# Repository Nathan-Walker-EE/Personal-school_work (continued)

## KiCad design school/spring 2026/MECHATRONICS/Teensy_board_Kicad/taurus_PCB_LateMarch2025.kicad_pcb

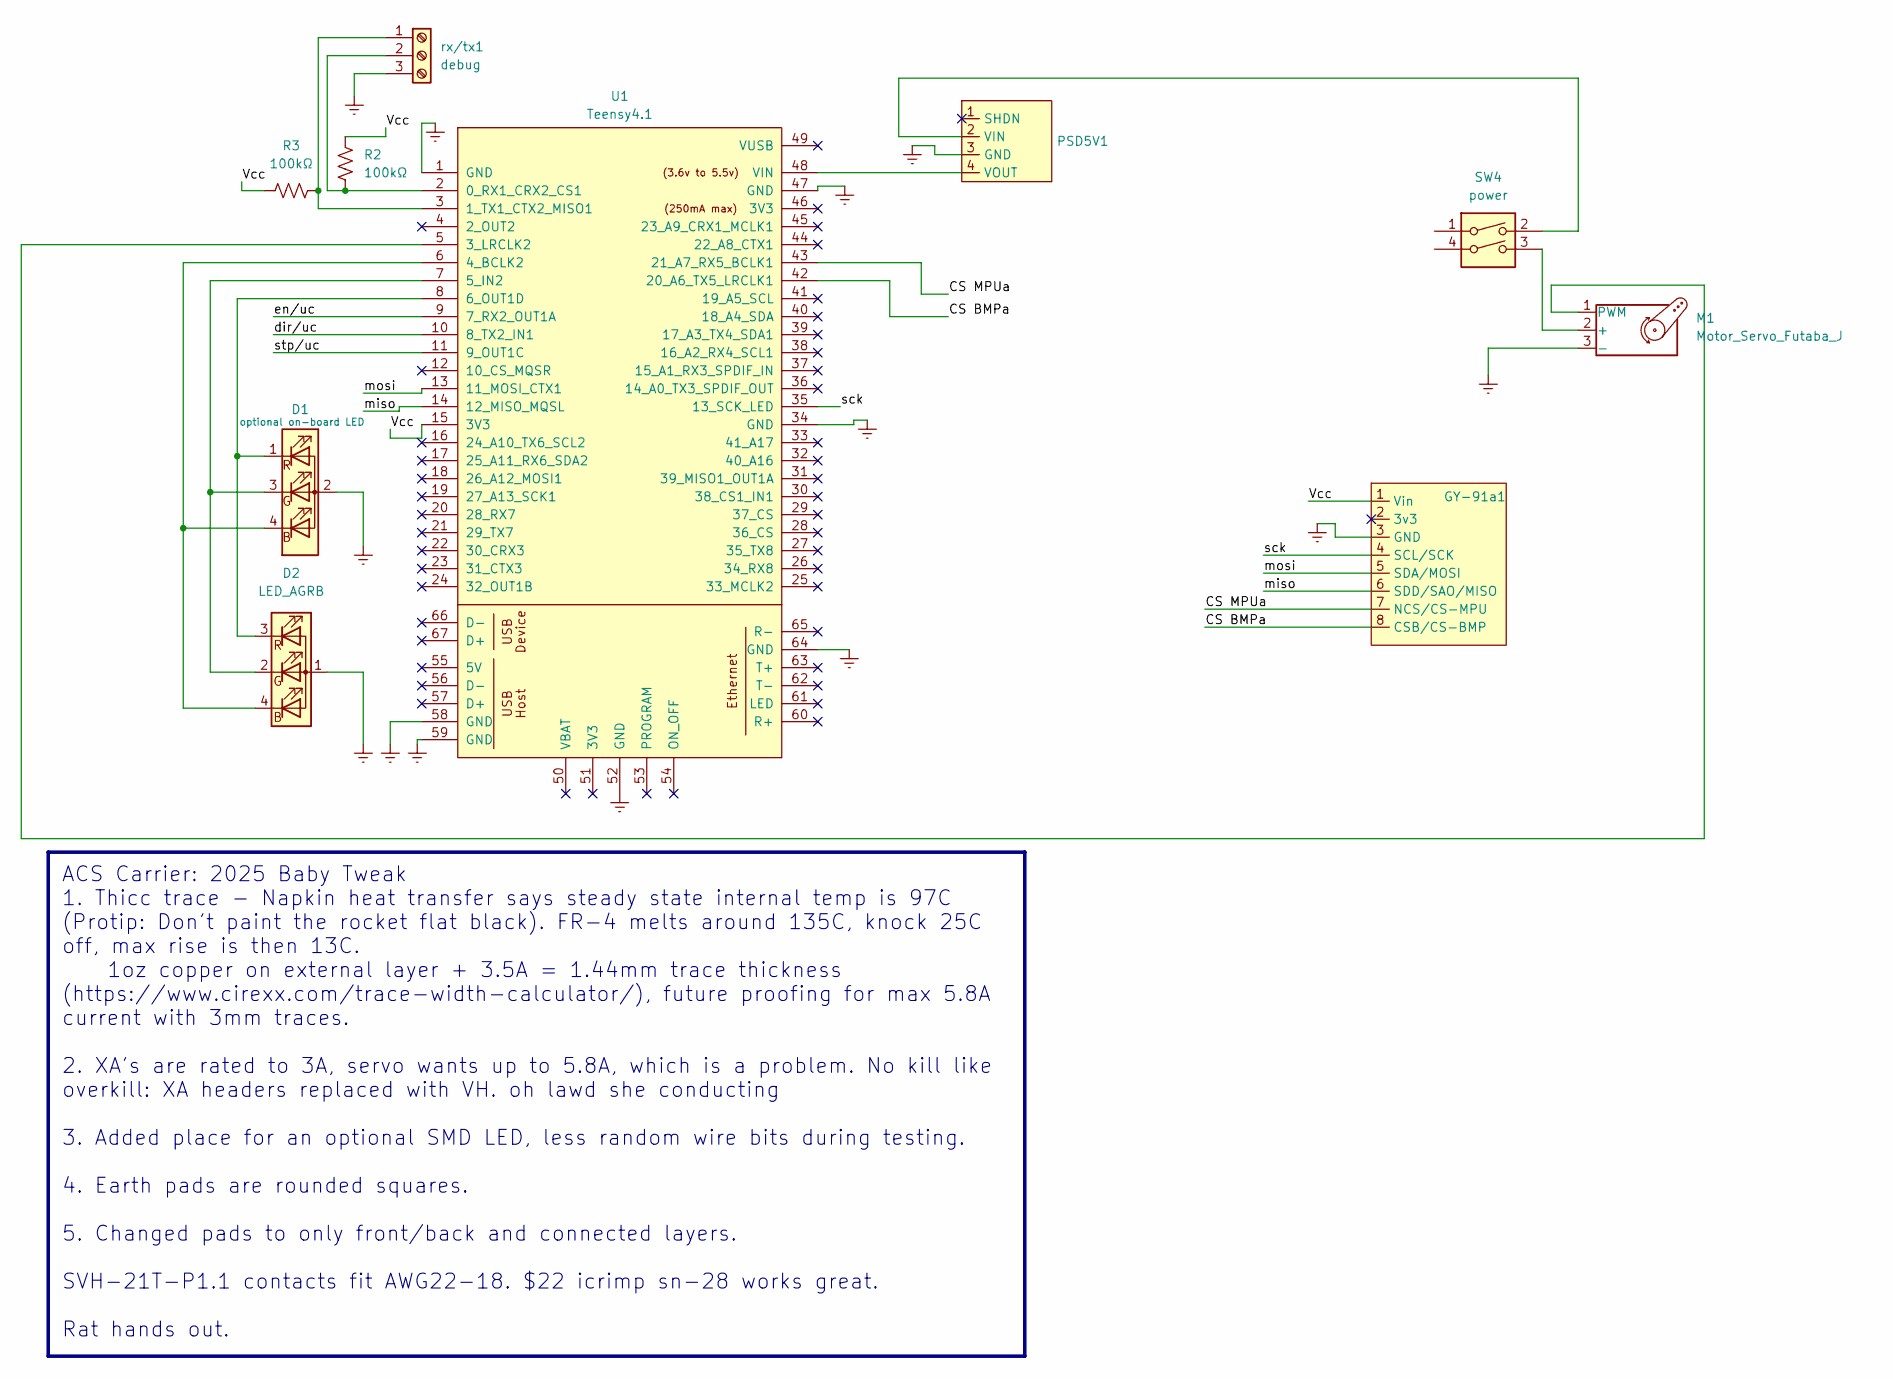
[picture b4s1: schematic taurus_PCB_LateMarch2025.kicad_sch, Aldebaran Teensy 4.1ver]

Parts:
D1: optional on-board LED; LED_Avago_PLCC4_3.2x2.8mm_CW
D2: LED_AGRB; JST_XA_B04B-XASK-1-A_1x04_P2.50mm_Vertical
GY-91a1: GY-91 carrier
M1: Motor_Servo_Futaba_J; JST_VH_B3P-VH-FB-B_1x03_P3.96mm_Vertical
PSD5V1: Pololu 5V0.6A stepdown
R2, R3: 100kΩ; C_0805_2012Metric_Pad1.18x1.45mm_HandSolder
SW4: power; JST_VH_B4P-VH-FB-B_1x04_P3.96mm_Vertical
U1: Teensy4.1; Teensy41
rx/tx1: debug; JST_VH_B3P-VH-FB-B_1x03_P3.96mm_Vertical

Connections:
/CS BMPa: GY-91a1.8 (CSB/CS-BMP), U1.42 (20_A6_TX5_LRCLK1)
/CS MPUa: GY-91a1.7 (NCS/CS-MPU), U1.43 (21_A7_RX5_BCLK1)
/Vcc: GY-91a1.1 (Vin), R2.2, R3.1, U1.15 (3V3)
/dir/uc: U1.10 (8_TX2_IN1)
/en/uc: U1.9 (7_RX2_OUT1A)
/miso: GY-91a1.6 (SDD/SAO/MISO), U1.14 (12_MISO_MQSL)
/mosi: GY-91a1.5 (SDA/MOSI), U1.13 (11_MOSI_CTX1)
/sck: GY-91a1.4 (SCL/SCK), U1.35 (13_SCK_LED)
/stp/uc: U1.11 (9_OUT1C)
Earth: D1.2 (A), D2.1 (A), GY-91a1.3 (GND), M1.3 (-), PSD5V1.3 (GND), SW4.1, SW4.4, U1.1 (GND), U1.34 (GND), U1.47 (GND), U1.52 (GND), U1.58 (GND), U1.59 (GND), U1.64 (GND), rx/tx1.3
unnamed: D1.4 (BK), D2.4 (BK), U1.6 (4_BCLK2)
unnamed: D1.3 (GK), D2.2 (GK), U1.7 (5_IN2)
unnamed: D1.1 (RK), D2.3 (RK), U1.8 (6_OUT1D)
unnamed: M1.2 (+), SW4.3
unnamed: M1.1 (PWM), U1.5 (3_LRCLK2)
unnamed: PSD5V1.2 (VIN), SW4.2
unnamed: PSD5V1.4 (VOUT), U1.48 (VIN)
unnamed: R2.1, U1.2 (0_RX1_CRX2_CS1), rx/tx1.2
unnamed: R3.2, U1.3 (1_TX1_CTX2_MISO1), rx/tx1.1

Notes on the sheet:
ACS Carrier: 2025 Baby Tweak 1. Thicc trace - Napkin heat transfer says steady state internal temp is 97C (Protip: Don't paint the rocket flat black). FR-4 melts around 135C, knock 25C off, max rise is then 13C. 1oz copper on external layer + 3.5A = 1.44mm trace thickness (https://www.cirexx.com/tr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

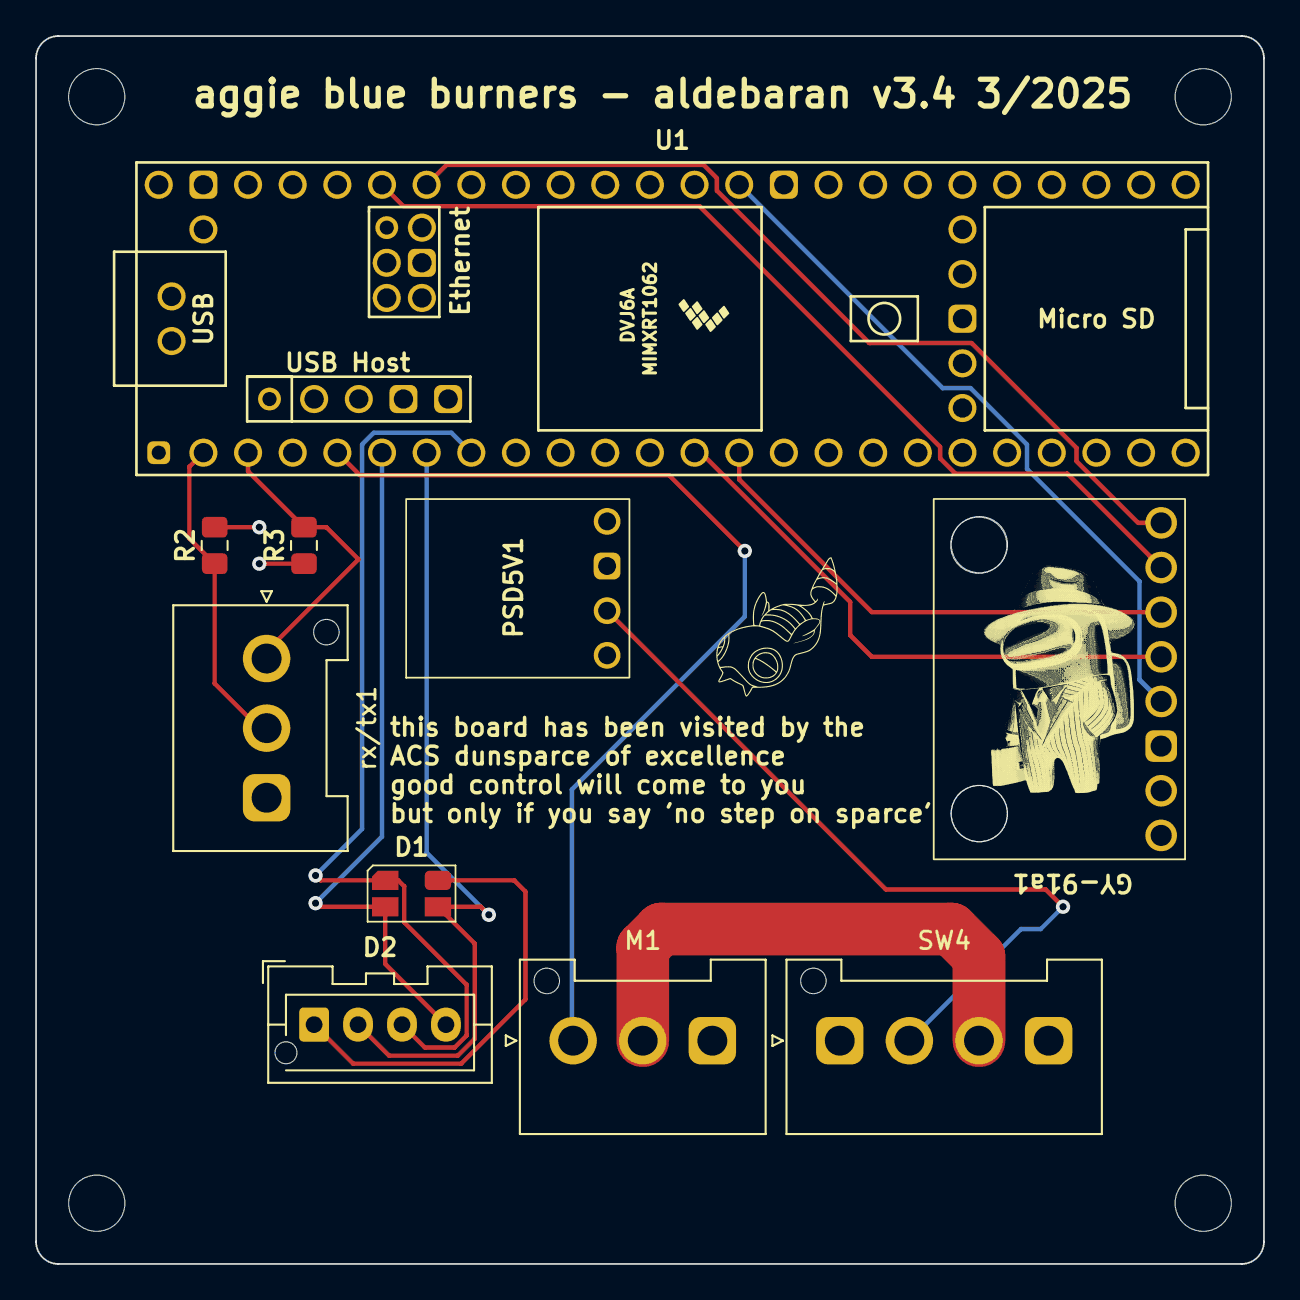
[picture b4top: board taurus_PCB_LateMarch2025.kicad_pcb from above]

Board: 4 copper layers, 69.9 x 69.9 mm, 14 parts (0 on the bottom side), 16 nets.

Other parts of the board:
refhole1, refhole2, refhole3, refhole4: MountingHole_3.2mm_M3

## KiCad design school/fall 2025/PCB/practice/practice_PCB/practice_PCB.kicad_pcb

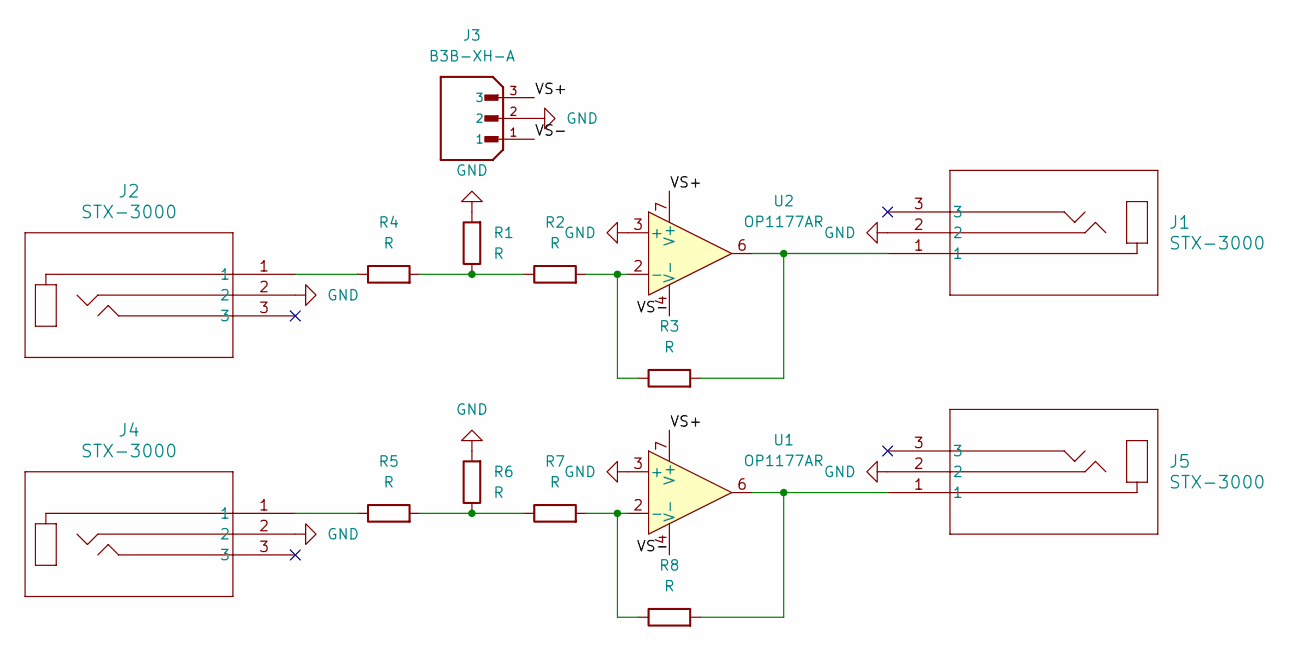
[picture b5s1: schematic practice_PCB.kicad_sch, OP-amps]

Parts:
J1, J2, J4, J5: STX-3000; STX-3000_KYC
J3: B3B-XH-A; JST_B3B-XH-A; PARTREV 7/4/21
R1, R2, R3, R4, R5, R6, R7, R8: R; R_0201_0603Metric
U1, U2: OP1177AR; SOIC-8_3.9x4.9mm_P1.27mm

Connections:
/VS+: J3.3, U1.7 (V+), U2.7 (V+)
/VS-: J3.1, U1.4 (V-), U2.4 (V-)
GND: J1.2, J2.2, J3.2, J4.2, J5.2, R1.2, R6.2, U1.3 (+), U2.3 (+)
unnamed: J1.1, R3.2, U2.6
unnamed: J2.1, R4.1
unnamed: J4.1, R5.1
unnamed: J5.1, R8.2, U1.6
unnamed: R1.1, R2.1, R4.2
unnamed: R5.2, R6.1, R7.1
unnamed: R7.2, R8.1, U1.2 (-)
unnamed: R2.2, R3.1, U2.2 (-)

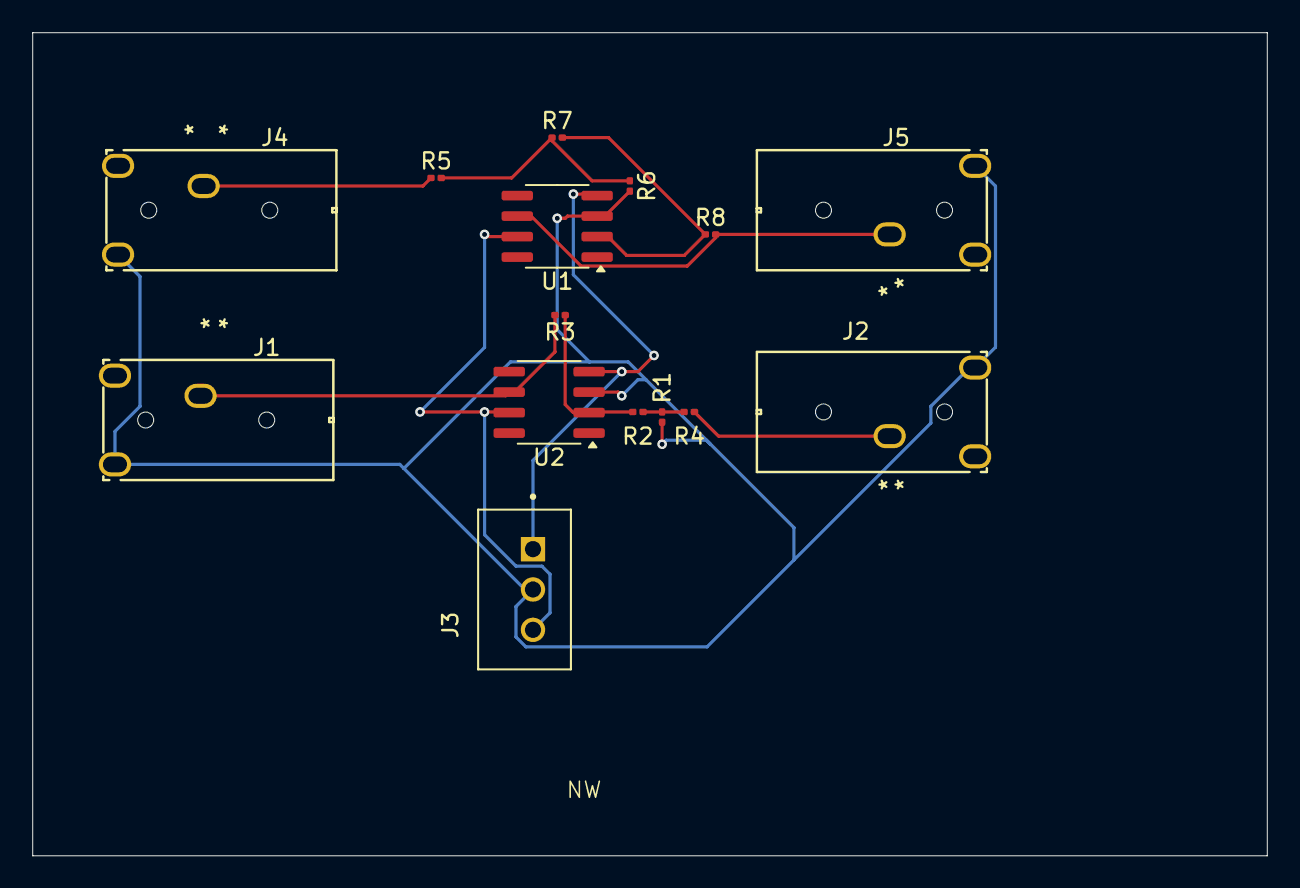
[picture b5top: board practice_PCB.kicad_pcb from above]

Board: 2 copper layers, 76.5 x 51.0 mm, 15 parts (0 on the bottom side), 11 nets.

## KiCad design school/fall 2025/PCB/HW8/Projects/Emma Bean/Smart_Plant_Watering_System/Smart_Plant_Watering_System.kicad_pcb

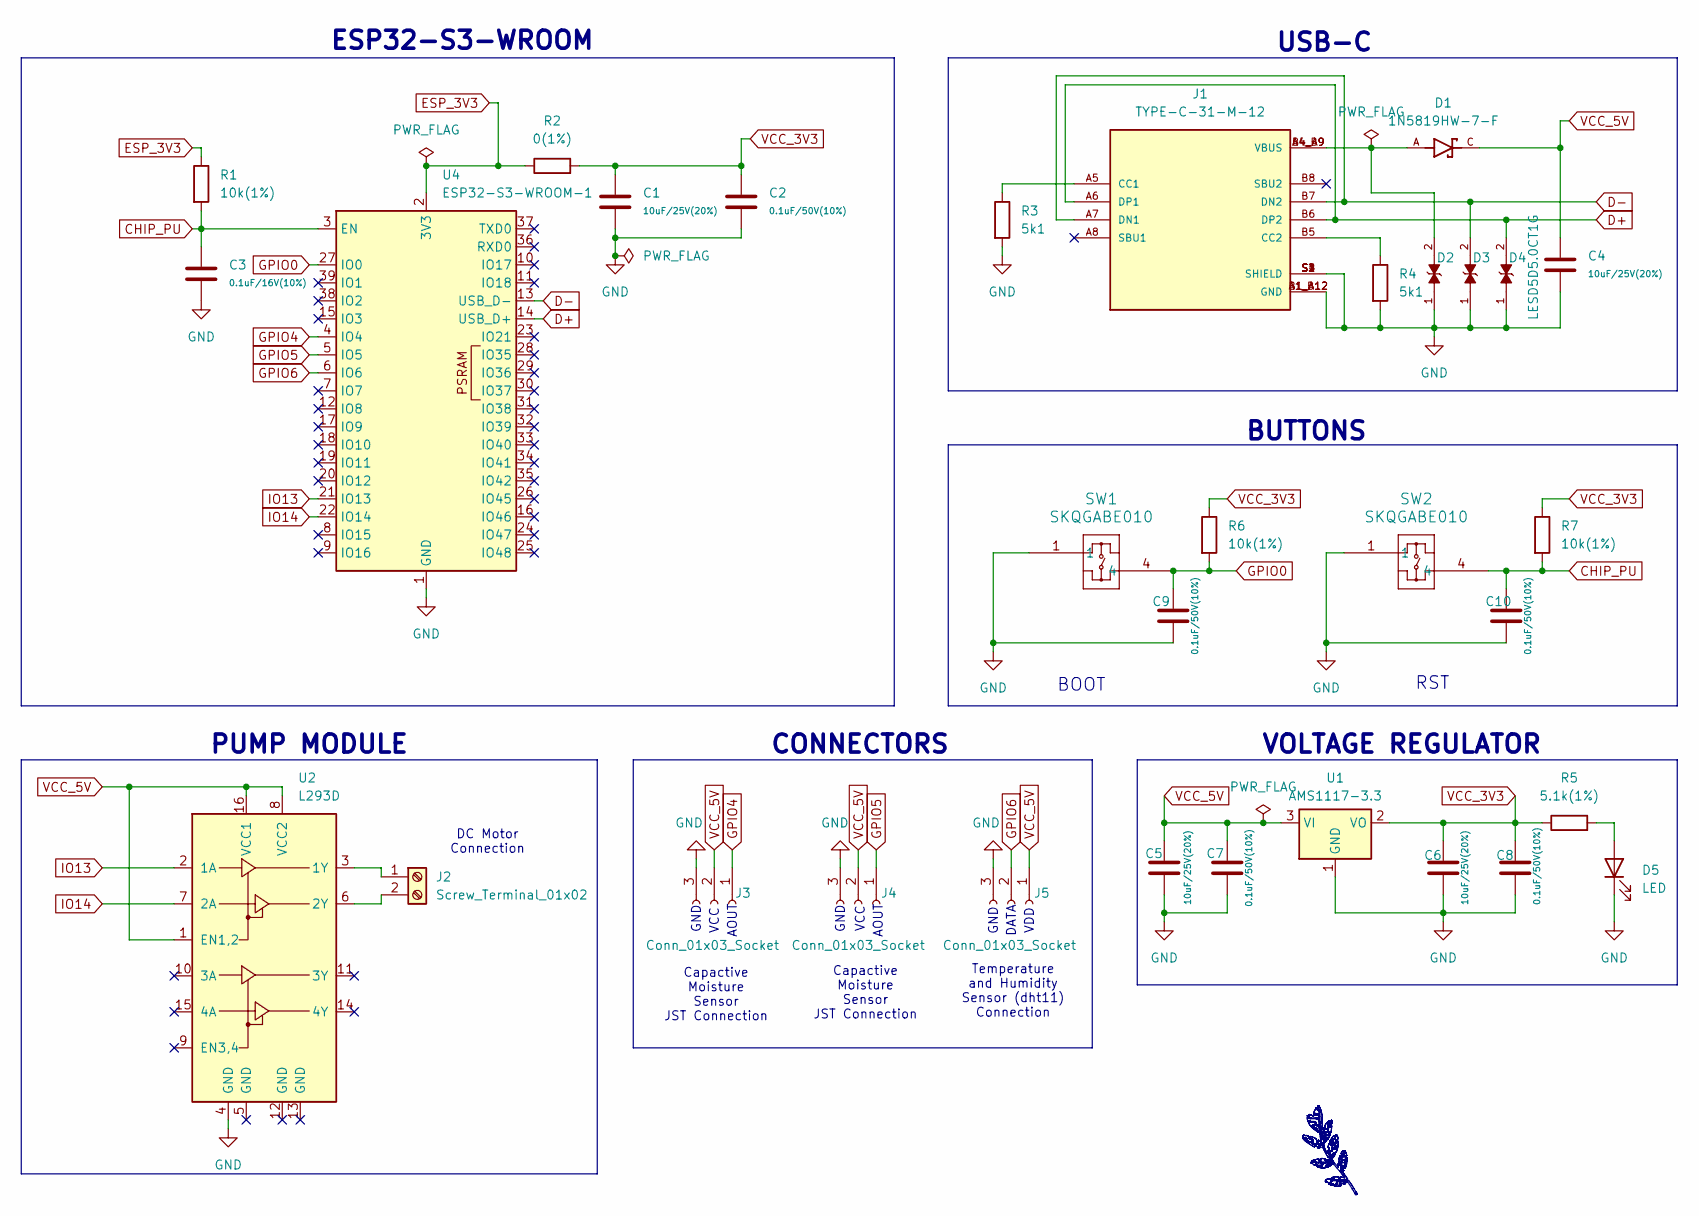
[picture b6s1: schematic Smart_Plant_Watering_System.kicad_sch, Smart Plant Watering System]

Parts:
C1, C4, C5, C6: 10uF/25V(20%); C_0805_2012Metric_Pad1.18x1.45mm_HandSolder
C2, C7, C8, C9, C10: 0.1uF/50V(10%); C_0805_2012Metric_Pad1.18x1.45mm_HandSolder
C3: 0.1uF/16V(10%); C_0805_2012Metric_Pad1.18x1.45mm_HandSolder
D1: 1N5819HW-7-F; SOD3715X145N; PARTREV 18-2; DigiKey_Part_Number 1N5819HW-FDICT-ND
D2, D3, D4: LESD5D5.0CT1G; D_SOD-523; PARTREV O
D5: LED; LED_0201_0603Metric
J1: TYPE-C-31-M-12; HRO_TYPE-C-31-M-12; PARTREV 2020.12.08
J2: Screw_Terminal_01x02; 691137710002
J3, J4, J5: Conn_01x03_Socket; JST_XH_B3B-XH-A_1x03_P2.50mm_Vertical
R1, R6, R7: 10k(1%); R_0805_2012Metric_Pad1.20x1.40mm_HandSolder
R2: 0(1%); R_0805_2012Metric_Pad1.20x1.40mm_HandSolder
R3, R4: 5k1; R_0805_2012Metric_Pad1.20x1.40mm_HandSolder
R5: 5.1k(1%); R_0805_2012Metric_Pad1.20x1.40mm_HandSolder
SW1, SW2: SKQGABE010; SKQGABE010_ALPS
U1: AMS1117-3.3; SOT-223-3_TabPin2
U2: L293D; DIP-16_W7.62mm
U4: ESP32-S3-WROOM-1

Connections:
CHIP_PU: C3.1, C10.1, R1.2, R7.2, SW2.4, U4.3 (EN)
D+: D4.2, J1.A6 (DP1), J1.B6 (DP2), U4.14 (USB_D+)
D-: D3.2, J1.A7 (DN1), J1.B7 (DN2), U4.13 (USB_D-)
ESP_3V3: R1.1, R2.1, U4.2 (3V3)
GND: C1.2, C2.2, C3.2, C4.2, C5.2, C6.2, C7.2, C8.2, C9.2, C10.2, D2.1, D3.1, D4.1, D5.1 (K), J1.A1_B12 (GND), J1.B1_A12 (GND), J1.S1 (SHIELD), J1.S2 (SHIELD), J1.S3 (SHIELD), J1.S4 (SHIELD), J3.3, J4.3, J5.3, R3.2, R4.2, SW1.1, SW2.1, U1.1 (GND), U2.4 (GND), U4.1 (GND), U4.40 (GND), U4.41 (GND)
GPIO0: C9.1, R6.2, SW1.4, U4.27 (IO0)
GPIO4: J3.1, U4.4 (IO4)
GPIO5: J4.1, U4.5 (IO5)
GPIO6: J5.2, U4.6 (IO6)
IO13: U2.2 (1A), U4.21 (IO13)
IO14: U2.7 (2A), U4.22 (IO14)
unnamed: D1.A, D2.2, J1.A4_B9 (VBUS), J1.B4_A9 (VBUS)
unnamed: D5.2 (A), R5.2
unnamed: J1.A5 (CC1), R3.1
unnamed: J1.B5 (CC2), R4.1
unnamed: J2.1, U2.3 (1Y)
unnamed: J2.2, U2.6 (2Y)
VCC_3V3: C1.1, C2.1, C6.1, C8.1, R2.2, R5.1, R6.1, R7.1, U1.2 (VO)
VCC_5V: C4.1, C5.1, C7.1, D1.C, J3.2, J4.2, J5.1, U1.3 (VI), U2.1 (EN1,2), U2.8 (VCC2), U2.16 (VCC1)

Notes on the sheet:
RST
AOUT
USB-C
BUTTONS
BOOT
VCC
DC Motor Connection
GND
DATA
CONNECTORS
Temperature and Humidity Sensor (dht11) Connection
ESP32-S3-WROOM
Capactive Moisture Sensor JST Connection
PUMP MODULE
VDD
VOLTAGE REGULATOR

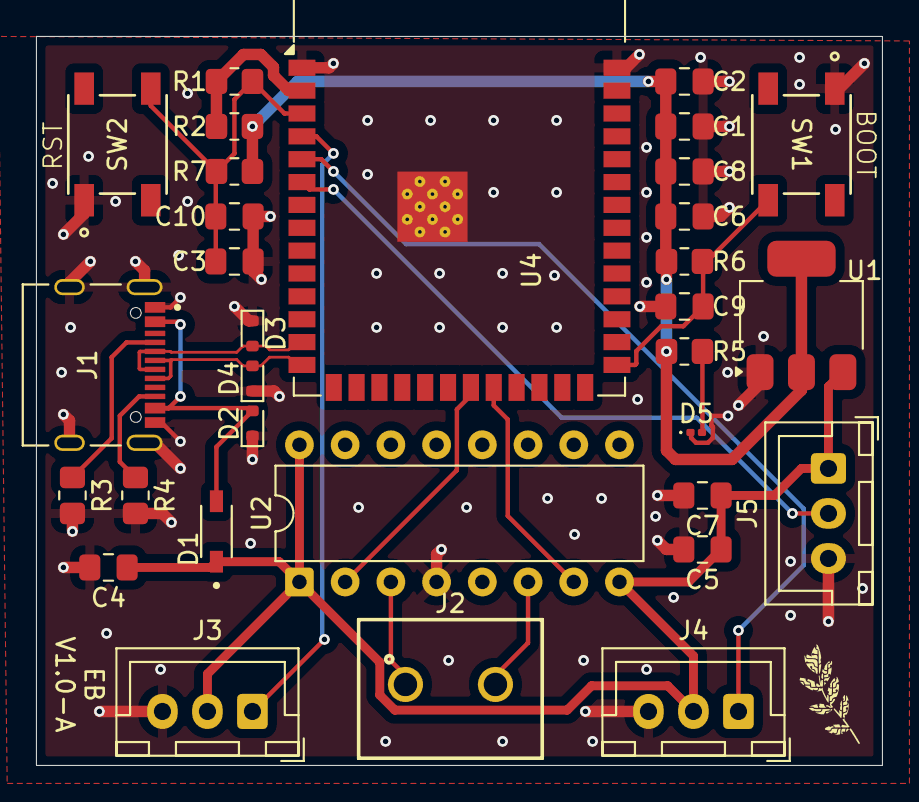
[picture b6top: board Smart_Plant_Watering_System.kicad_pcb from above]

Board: 2 copper layers, 47.0 x 40.5 mm, 32 parts (0 on the bottom side), 19 nets.

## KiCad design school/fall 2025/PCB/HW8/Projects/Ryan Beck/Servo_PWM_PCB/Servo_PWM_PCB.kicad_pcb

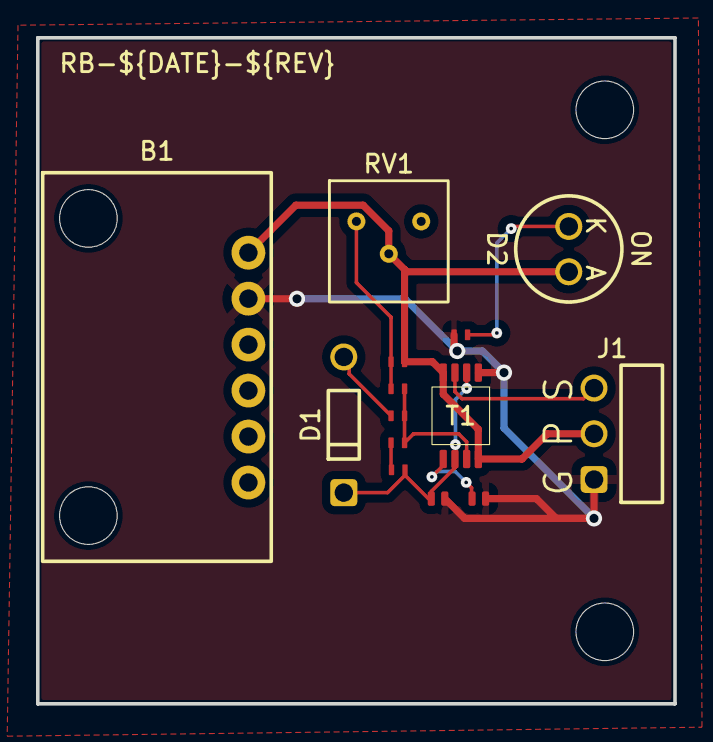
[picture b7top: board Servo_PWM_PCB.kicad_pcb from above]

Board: 2 copper layers, 35.4 x 37.0 mm, 16 parts (0 on the bottom side), 10 nets.

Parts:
B1: USB-C-Breakout_w_5.1k_pulldowns
C1: 10n; 103_3372_0402B103K500HI
C2: 100n; 104_3372_0402B104K250HI
D1: 1n914_Signal_Diode
D2: ON; LED_5MM_Discrete
J1: Conn_01x03_Pin; 3x_Pin_Connector
MH_1, MH_3: M3_Screw_Hole
R1: 3.3K; 0402_RN73H
R2: 200K; 0402_RN73H
R3: 1K; 0402_RN73H
R4: 18K; 0402_RN73H
R5: 220; 0402_RN73H
R6: 60K; 0402_RN73H
RV1: 100K; 3362H_Trim_Pot
T1: 27422_LM555_1

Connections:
5V: B1.1 (VBUS), D2.2 (A), J1.2, R4.1, RV1.2, T1.4 (RES), T1.8 (VCC)
GND: B1.2 (GND), C1.2, C2.2, J1.3 (G), R5.2, T1.1 (GND)
unnamed: D1.1, R1.1
unnamed: D2.1 (K), R5.1
unnamed: J1.1 (S), T1.3 (OUT)
unnamed: R2.1, R6.2
unnamed: R3.2, R4.2, RV1.1
unnamed: C1.1, T1.5 (CTL)
unnamed: R1.2, R2.2, R3.1, T1.7 (DIS)
unnamed: C2.1, D1.2, R6.1, T1.2 (TRG), T1.6 (THR)

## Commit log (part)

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2026-04-04 initial push
